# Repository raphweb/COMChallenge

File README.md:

# COMChallenge
Hardware and software parts for the COM challenge.

## Hardware
There is a base board to put up to 8 ESP32-C3 Minis on, including different COM transceivers. Currently, a TJA1050 CAN transceiver is supported. As an extra feature, there is a I²C bus controlled port expander to switch on/off the power for each of the 8 ESP32 modules. A hardware switch can override the port expaneder setting and provide power regardless. The base board can actually run two different COM busses, 4 for the top and 4 for the bottom ESP32 modules.

### Base Board Front:

### Base Board Back:

More details in the [hardware folder](/hardware/).

## Software
There are examples in the [software folder](/software/).

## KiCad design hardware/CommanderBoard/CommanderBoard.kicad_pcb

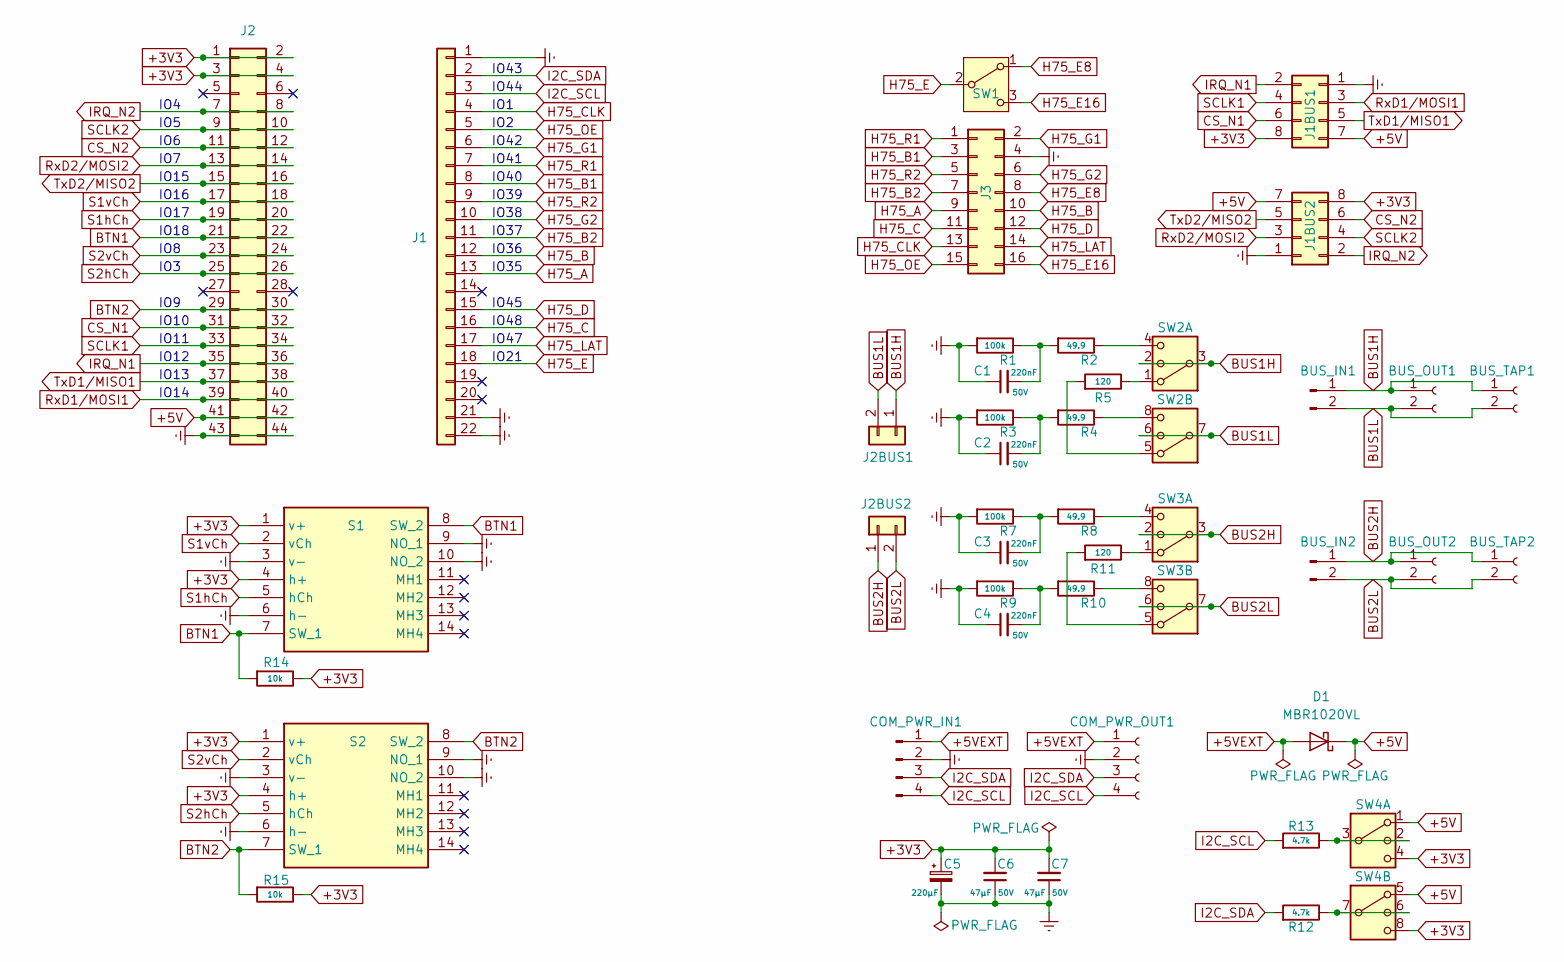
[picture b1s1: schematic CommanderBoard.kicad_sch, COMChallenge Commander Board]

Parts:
BUS_IN1, BUS_IN2: Conn_01x02_Pin; PinHeader_1x02_P2.54mm_Horizontal
BUS_OUT1, BUS_OUT2: Conn_01x02_Socket; PinSocket_1x02_P2.54mm_Horizontal
BUS_TAP1, BUS_TAP2: Conn_01x02_Socket; PinHeader_1x02_P2.54mm_Vertical
C1, C2, C3, C4: 220nF; C_0805_2012Metric; Voltage Rated 50V; Tolerance ±10%; Part CL05B104KB54PNC; LCSC C307331
C5: 220µF; CP_Radial_D6.3mm_P2.50mm
C6, C7: 47µF; C_0805_2012Metric; Voltage Rated 50V; Tolerance ±10%; Part CL05B104KB54PNC; LCSC C307331
COM_PWR_IN1: Conn_01x04_Pin; PinHeader_1x04_P2.54mm_Horizontal
COM_PWR_OUT1: Conn_01x04_Socket; PinSocket_1x04_P2.54mm_Horizontal
D1: MBR1020VL; D_SOD-123F
J1: Conn_01x22; PinSocket_1x22_P2.54mm_Vertical
J1BUS1, J1BUS2: Conn_02x04_Odd_Even; PinSocket_2x04_P2.54mm_Vertical
J2: Conn_02x22; PinSocket_2x22_P2.54mm_Vertical
J2BUS1, J2BUS2: Conn_01x02; PinSocket_1x02_P2.54mm_Vertical
J3: HUB75; IDC-Header_2x08_P2.54mm_Vertical
R1, R3, R7, R9: 100k; R_1206_3216Metric; Overload Voltage Max 200V; Tolerance ±1%; Part 1206W4F1002T5E; LCSC C17902
R2, R4, R8, R10: 49.9; R_1206_3216Metric; Overload Voltage Max 200V; Tolerance ±1%; Part 1206W4F1002T5E; LCSC C17902
R5, R11: 120; R_1206_3216Metric; Overload Voltage Max 200V; Tolerance ±1%; Part 1206W4F1002T5E; LCSC C17902
R12, R13: 4.7k; R_1206_3216Metric; Overload Voltage Max 200V; Tolerance ±1%; Part 1206W4F1002T5E; LCSC C17902
R14, R15: 10k; R_1206_3216Metric; Overload Voltage Max 200V; Tolerance ±1%; Part 1206W4F1002T5E; LCSC C17902
S1, S2: THB001P; Mouser Part Number 611-THB001P
SW1: SW_SPDT; CLSB12B01T
SW2, SW3, SW4: SW_DP3T; CLSB23B01T

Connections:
+3V3: C5.1, C6.2, C7.2, J1BUS1.8, J1BUS2.8, J2.1, J2.2, J2.3, J2.4, R14.1, R15.1, S1.1 (v+), S1.4 (h+), S2.1 (v+), S2.4 (h+), SW4.4, SW4.8
+5V: D1.1 (K), J1BUS1.7, J1BUS2.7, J2.41, J2.42, SW4.1, SW4.5
+5VEXT: COM_PWR_IN1.1, COM_PWR_OUT1.1, D1.2 (A)
BTN1: J2.21, J2.22, R14.2, S1.7 (SW_1), S1.8 (SW_2)
BTN2: J2.29, J2.30, R15.2, S2.7 (SW_1), S2.8 (SW_2)
BUS1H: BUS_IN1.1, BUS_OUT1.1, BUS_TAP1.1, J2BUS1.1, SW2.2, SW2.3
BUS1L: BUS_IN1.2, BUS_OUT1.2, BUS_TAP1.2, J2BUS1.2, SW2.6, SW2.7
BUS2H: BUS_IN2.1, BUS_OUT2.1, BUS_TAP2.1, J2BUS2.1, SW3.2, SW3.3
BUS2L: BUS_IN2.2, BUS_OUT2.2, BUS_TAP2.2, J2BUS2.2, SW3.6, SW3.7
CS_N1: J1BUS1.6, J2.31, J2.32
CS_N2: J1BUS2.6, J2.11, J2.12
GNDREF: C1.1, C2.1, C3.1, C4.1, C5.2, C6.1, C7.1, COM_PWR_IN1.2, COM_PWR_OUT1.2, J1.1, J1.21, J1.22, J1BUS1.1, J1BUS2.1, J2.43, J2.44, J3.4, R1.2, R3.2, R7.2, R9.2, S1.3 (v-), S1.6 (h-), S1.9 (NO_1), S1.10 (NO_2), S2.3 (v-), S2.6 (h-), S2.9 (NO_1), S2.10 (NO_2)
H75_A: J1.13, J3.9
H75_B: J1.12, J3.10
H75_B1: J1.8, J3.3
H75_B2: J1.11, J3.7
H75_C: J1.16, J3.11
H75_CLK: J1.4, J3.13
H75_D: J1.15, J3.12
H75_E: J1.18, SW1.2 (B)
H75_E8: J3.8, SW1.1 (A)
H75_E16: J3.16, SW1.3 (C)
H75_G1: J1.6, J3.2
H75_G2: J1.10, J3.6
H75_LAT: J1.17, J3.14
H75_OE: J1.5, J3.15
H75_R1: J1.7, J3.1
H75_R2: J1.9, J3.5
I2C_SCL: COM_PWR_IN1.4, COM_PWR_OUT1.4, J1.3, R13.2
I2C_SDA: COM_PWR_IN1.3, COM_PWR_OUT1.3, J1.2, R12.2
IRQ_N1: J1BUS1.2, J2.35, J2.36
IRQ_N2: J1BUS2.2, J2.7, J2.8
unnamed: C1.2, R1.1, R2.2
unnamed: C2.2, R3.1, R4.2
unnamed: C3.2, R7.1, R8.2
unnamed: C4.2, R9.1, R10.2
unnamed: R2.1, SW2.4
unnamed: R4.1, SW2.8
unnamed: R5.1, SW2.1
unnamed: R5.2, SW2.5
unnamed: R8.1, SW3.4
unnamed: R10.1, SW3.8
unnamed: R11.1, SW3.1
unnamed: R11.2, SW3.5
unnamed: R12.1, SW4.6, SW4.7
unnamed: R13.1, SW4.2, SW4.3
RxD1/MOSI1: J1BUS1.3, J2.39, J2.40
RxD2/MOSI2: J1BUS2.3, J2.13, J2.14
S1hCh: J2.19, J2.20, S1.5 (hCh)
S1vCh: J2.17, J2.18, S1.2 (vCh)
S2hCh: J2.25, J2.26, S2.5 (hCh)
S2vCh: J2.23, J2.24, S2.2 (vCh)
SCLK1: J1BUS1.4, J2.33, J2.34
SCLK2: J1BUS2.4, J2.9, J2.10
TxD1/MISO1: J1BUS1.5, J2.37, J2.38
TxD2/MISO2: J1BUS2.5, J2.15, J2.16

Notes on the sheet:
IO5
IO47
IO15
IO21
IO7
IO39
IO12
IO2
IO17
IO42
IO44
IO4
IO10
IO45
IO3
IO43
IO9
IO37
IO16
IO18
IO38
IO8
IO40
IO1
IO13
IO14
IO48
IO6
IO35
IO11
IO36
IO41

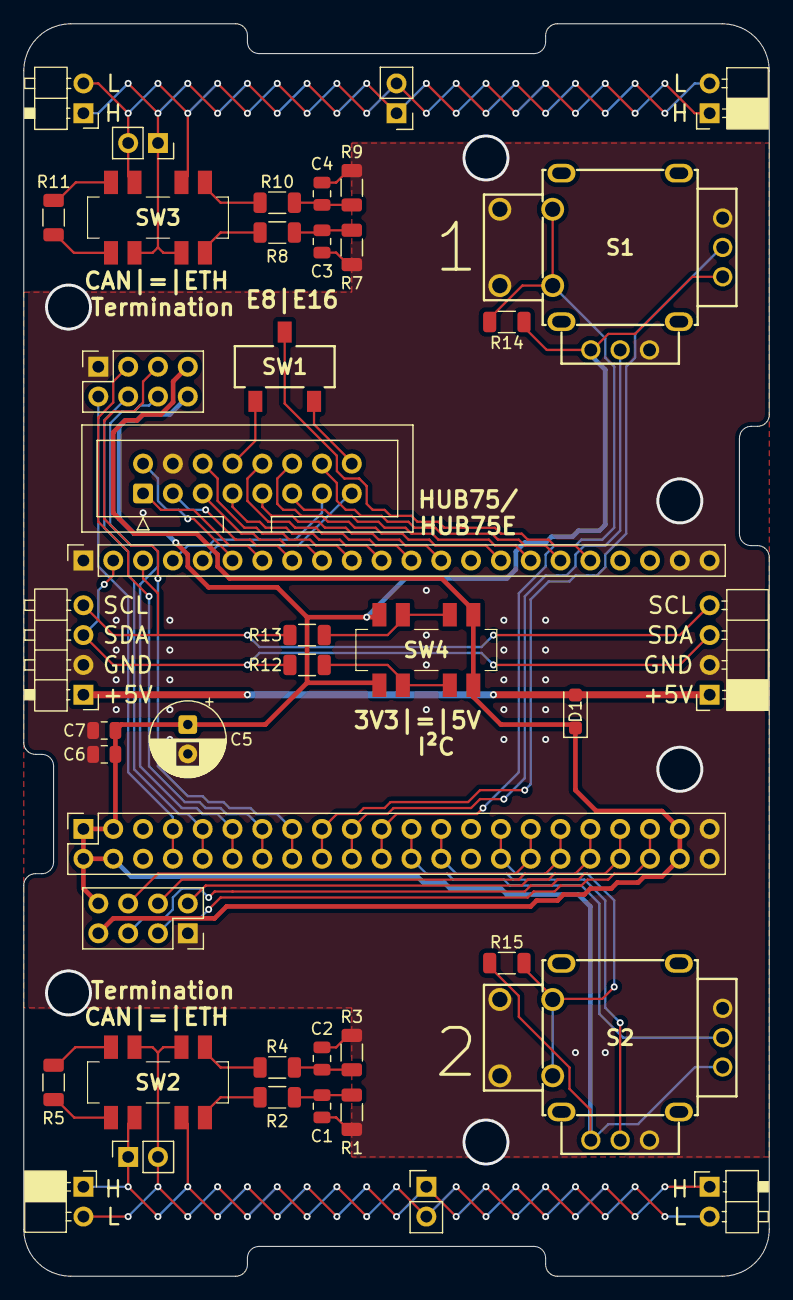
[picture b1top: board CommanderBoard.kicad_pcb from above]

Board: 2 copper layers, 63.5 x 106.7 mm, 43 parts (0 on the bottom side), 56 nets.

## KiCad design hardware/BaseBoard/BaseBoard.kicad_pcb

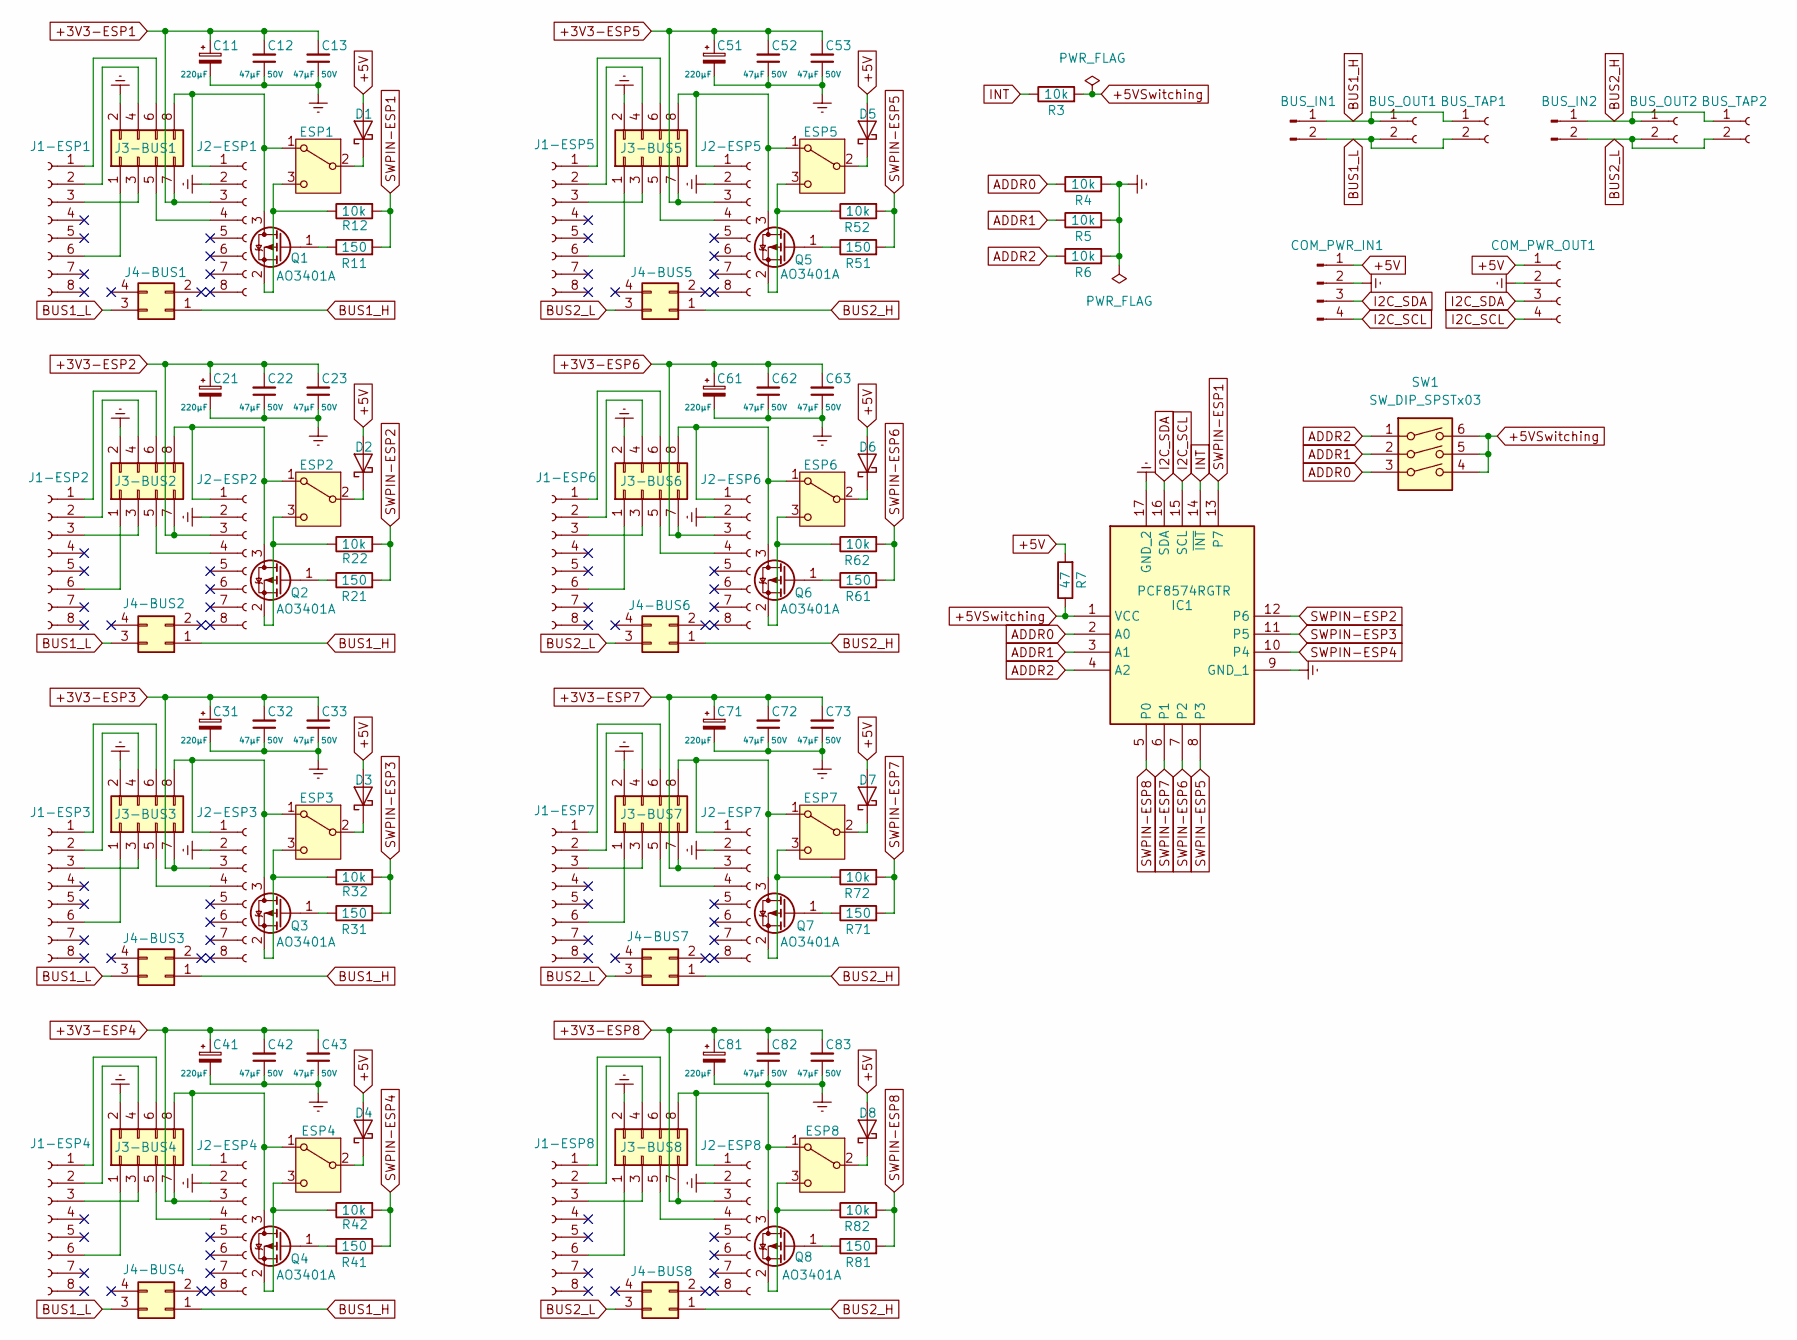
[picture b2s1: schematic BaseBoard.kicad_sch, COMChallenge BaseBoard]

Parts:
BUS_IN1, BUS_IN2: Conn_01x02_Pin; PinHeader_1x02_P2.54mm_Horizontal
BUS_OUT1, BUS_OUT2: Conn_01x02_Socket; PinSocket_1x02_P2.54mm_Horizontal
BUS_TAP1, BUS_TAP2: Conn_01x02_Socket; PinHeader_1x02_P2.54mm_Vertical
C11, C21, C31, C41, C51, C61, C71, C81: 220µF; CP_Radial_D6.3mm_P2.50mm
C12, C13, C22, C23, C32, C33, C42, C43, C52, C53, C62, C63, C72, C73, C82, C83: 47µF; C_0805_2012Metric; Voltage Rated 50V; Tolerance ±10%; Part CL05B104KB54PNC; LCSC C307331
COM_PWR_IN1: Conn_01x04_Pin; PinHeader_1x04_P2.54mm_Horizontal
COM_PWR_OUT1: Conn_01x04_Socket; PinSocket_1x04_P2.54mm_Horizontal
D1, D2, D3, D4, D5, D6, D7, D8: MBR1020VL; D_SOD-123F
ESP1, ESP2, ESP3, ESP4, ESP5, ESP6, ESP7, ESP8: SW_DPDT_XLX_MHPS2285; CLSB12B01T
IC1: PCF8574RGTR; QFN50P300X300X100-17N-D; Mouser Part Number 595-PCF8574RGTR
J1-ESP1, J1-ESP2, J1-ESP3, J1-ESP4, J1-ESP5, J1-ESP6, J1-ESP7, J1-ESP8: ESP-1-L; PinSocket_1x08_P2.54mm_Vertical
J2-ESP1, J2-ESP2, J2-ESP3, J2-ESP4, J2-ESP5, J2-ESP6, J2-ESP7, J2-ESP8: ESP-1-R; PinSocket_1x08_P2.54mm_Vertical
J3-BUS1, J3-BUS2, J3-BUS3, J3-BUS4, J3-BUS5, J3-BUS6, J3-BUS7, J3-BUS8: BUS-IN; Wuerth_WR-PHD_61300825721_Standard_2x04_P2.54mm_Vertical
J4-BUS1, J4-BUS2, J4-BUS3, J4-BUS4, J4-BUS5, J4-BUS6, J4-BUS7, J4-BUS8: BUS-OUT; Wuerth_WR-PHD_61300425721_Standard_2x02_P2.54mm_Vertical
Q1, Q2, Q3, Q4, Q5, Q6, Q7, Q8: AO3401A; SOT-23
R3, R4, R5, R6: 10k; R_0402_1005Metric
R7: 47; R_0603_1608Metric
R11, R21, R31, R41, R51, R61, R71, R81: 150; R_0805_2012Metric
R12, R22, R32, R42, R52, R62, R72, R82: 10k; R_0805_2012Metric
SW1: SW_DIP_SPSTx03; SW_DIP_SPSTx03_Slide_6.7x9.18mm_W8.61mm_P2.54mm_LowProfile

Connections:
+3V3-ESP1: C11.1, C12.2, C13.2, J2-ESP1.3, J3-BUS1.7
+3V3-ESP2: C21.1, C22.2, C23.2, J2-ESP2.3, J3-BUS2.7
+3V3-ESP3: C31.1, C32.2, C33.2, J2-ESP3.3, J3-BUS3.7
+3V3-ESP4: C41.1, C42.2, C43.2, J2-ESP4.3, J3-BUS4.7
+3V3-ESP5: C51.1, C52.2, C53.2, J2-ESP5.3, J3-BUS5.7
+3V3-ESP6: C61.1, C62.2, C63.2, J2-ESP6.3, J3-BUS6.7
+3V3-ESP7: C71.1, C72.2, C73.2, J2-ESP7.3, J3-BUS7.7
+3V3-ESP8: C81.1, C82.2, C83.2, J2-ESP8.3, J3-BUS8.7
+5V: COM_PWR_IN1.1, COM_PWR_OUT1.1, D1.2 (A), D2.2 (A), D3.2 (A), D4.2 (A), D5.2 (A), D6.2 (A), D7.2 (A), D8.2 (A), R7.2
+5VSwitching: IC1.1 (VCC), R3.2, R7.1, SW1.4, SW1.5, SW1.6
ADDR0: IC1.2 (A0), R4.1, SW1.3
ADDR1: IC1.3 (A1), R5.1, SW1.2
ADDR2: IC1.4 (A2), R6.1, SW1.1
BUS1_H: BUS_IN1.1, BUS_OUT1.1, BUS_TAP1.1, J4-BUS1.1, J4-BUS2.1, J4-BUS3.1, J4-BUS4.1
BUS1_L: BUS_IN1.2, BUS_OUT1.2, BUS_TAP1.2, J4-BUS1.3, J4-BUS2.3, J4-BUS3.3, J4-BUS4.3
BUS2_H: BUS_IN2.1, BUS_OUT2.1, BUS_TAP2.1, J4-BUS5.1, J4-BUS6.1, J4-BUS7.1, J4-BUS8.1
BUS2_L: BUS_IN2.2, BUS_OUT2.2, BUS_TAP2.2, J4-BUS5.3, J4-BUS6.3, J4-BUS7.3, J4-BUS8.3
GNDREF: C11.2, C12.1, C13.1, C21.2, C22.1, C23.1, C31.2, C32.1, C33.1, C41.2, C42.1, C43.1, C51.2, C52.1, C53.1, C61.2, C62.1, C63.1, C71.2, C72.1, C73.1, C81.2, C82.1, C83.1, COM_PWR_IN1.2, COM_PWR_OUT1.2, IC1.9 (GND_1), IC1.17 (GND_2), J2-ESP1.2, J2-ESP2.2, J2-ESP3.2, J2-ESP4.2, J2-ESP5.2, J2-ESP6.2, J2-ESP7.2, J2-ESP8.2, J3-BUS1.2, J3-BUS2.2, J3-BUS3.2, J3-BUS4.2, J3-BUS5.2, J3-BUS6.2, J3-BUS7.2, J3-BUS8.2, R4.2, R5.2, R6.2
I2C_SCL: COM_PWR_IN1.4, COM_PWR_OUT1.4, IC1.15 (SCL)
I2C_SDA: COM_PWR_IN1.3, COM_PWR_OUT1.3, IC1.16 (SDA)
INT: IC1.14 (~INT), R3.1
unnamed: D1.1 (K), ESP1.2 (B)
unnamed: D2.1 (K), ESP2.2 (B)
unnamed: D3.1 (K), ESP3.2 (B)
unnamed: D4.1 (K), ESP4.2 (B)
unnamed: D5.1 (K), ESP5.2 (B)
unnamed: D6.1 (K), ESP6.2 (B)
unnamed: D7.1 (K), ESP7.2 (B)
unnamed: D8.1 (K), ESP8.2 (B)
unnamed: ESP1.1 (A), J2-ESP1.1, J3-BUS1.8, Q1.3 (D)
unnamed: ESP1.3 (C), Q1.2 (S), R12.1
unnamed: ESP2.1 (A), J2-ESP2.1, J3-BUS2.8, Q2.3 (D)
unnamed: ESP2.3 (C), Q2.2 (S), R22.1
unnamed: ESP3.1 (A), J2-ESP3.1, J3-BUS3.8, Q3.3 (D)
unnamed: ESP3.3 (C), Q3.2 (S), R32.1
unnamed: ESP4.1 (A), J2-ESP4.1, J3-BUS4.8, Q4.3 (D)
unnamed: ESP4.3 (C), Q4.2 (S), R42.1
unnamed: ESP5.1 (A), J2-ESP5.1, J3-BUS5.8, Q5.3 (D)
unnamed: ESP5.3 (C), Q5.2 (S), R52.1
unnamed: ESP6.1 (A), J2-ESP6.1, J3-BUS6.8, Q6.3 (D)
unnamed: ESP6.3 (C), Q6.2 (S), R62.1
unnamed: ESP7.1 (A), J2-ESP7.1, J3-BUS7.8, Q7.3 (D)
unnamed: ESP7.3 (C), Q7.2 (S), R72.1
unnamed: ESP8.1 (A), J2-ESP8.1, J3-BUS8.8, Q8.3 (D)
unnamed: ESP8.3 (C), Q8.2 (S), R82.1
unnamed: J1-ESP1.1, J3-BUS1.6
unnamed: J1-ESP1.2, J3-BUS1.4
unnamed: J1-ESP1.3, J3-BUS1.3
unnamed: J1-ESP1.6, J3-BUS1.1
unnamed: J1-ESP2.1, J3-BUS2.6
unnamed: J1-ESP2.2, J3-BUS2.4
unnamed: J1-ESP2.3, J3-BUS2.3
unnamed: J1-ESP2.6, J3-BUS2.1
unnamed: J1-ESP3.1, J3-BUS3.6
unnamed: J1-ESP3.2, J3-BUS3.4
unnamed: J1-ESP3.3, J3-BUS3.3
unnamed: J1-ESP3.6, J3-BUS3.1
unnamed: J1-ESP4.1, J3-BUS4.6
unnamed: J1-ESP4.2, J3-BUS4.4
unnamed: J1-ESP4.3, J3-BUS4.3
unnamed: J1-ESP4.6, J3-BUS4.1
unnamed: J1-ESP5.1, J3-BUS5.6
unnamed: J1-ESP5.2, J3-BUS5.4
unnamed: J1-ESP5.3, J3-BUS5.3
unnamed: J1-ESP5.6, J3-BUS5.1
unnamed: J1-ESP6.1, J3-BUS6.6
unnamed: J1-ESP6.2, J3-BUS6.4
unnamed: J1-ESP6.3, J3-BUS6.3
unnamed: J1-ESP6.6, J3-BUS6.1
unnamed: J1-ESP7.1, J3-BUS7.6
unnamed: J1-ESP7.2, J3-BUS7.4
unnamed: J1-ESP7.3, J3-BUS7.3
unnamed: J1-ESP7.6, J3-BUS7.1
unnamed: J1-ESP8.1, J3-BUS8.6
unnamed: J1-ESP8.2, J3-BUS8.4
unnamed: J1-ESP8.3, J3-BUS8.3
unnamed: J1-ESP8.6, J3-BUS8.1
unnamed: J2-ESP1.4, J3-BUS1.5
unnamed: J2-ESP2.4, J3-BUS2.5
unnamed: J2-ESP3.4, J3-BUS3.5
unnamed: J2-ESP4.4, J3-BUS4.5
unnamed: J2-ESP5.4, J3-BUS5.5
unnamed: J2-ESP6.4, J3-BUS6.5
unnamed: J2-ESP7.4, J3-BUS7.5
unnamed: J2-ESP8.4, J3-BUS8.5
unnamed: Q1.1 (G), R11.1
unnamed: Q2.1 (G), R21.1
unnamed: Q3.1 (G), R31.1
unnamed: Q4.1 (G), R41.1
unnamed: Q5.1 (G), R51.1
unnamed: Q6.1 (G), R61.1
unnamed: Q7.1 (G), R71.1
unnamed: Q8.1 (G), R81.1
SWPIN-ESP1: IC1.13 (P7), R11.2, R12.2
SWPIN-ESP2: IC1.12 (P6), R21.2, R22.2
SWPIN-ESP3: IC1.11 (P5), R31.2, R32.2
SWPIN-ESP4: IC1.10 (P4), R41.2, R42.2
SWPIN-ESP5: IC1.8 (P3), R51.2, R52.2
SWPIN-ESP6: IC1.7 (P2), R61.2, R62.2
SWPIN-ESP7: IC1.6 (P1), R71.2, R72.2
SWPIN-ESP8: IC1.5 (P0), R81.2, R82.2

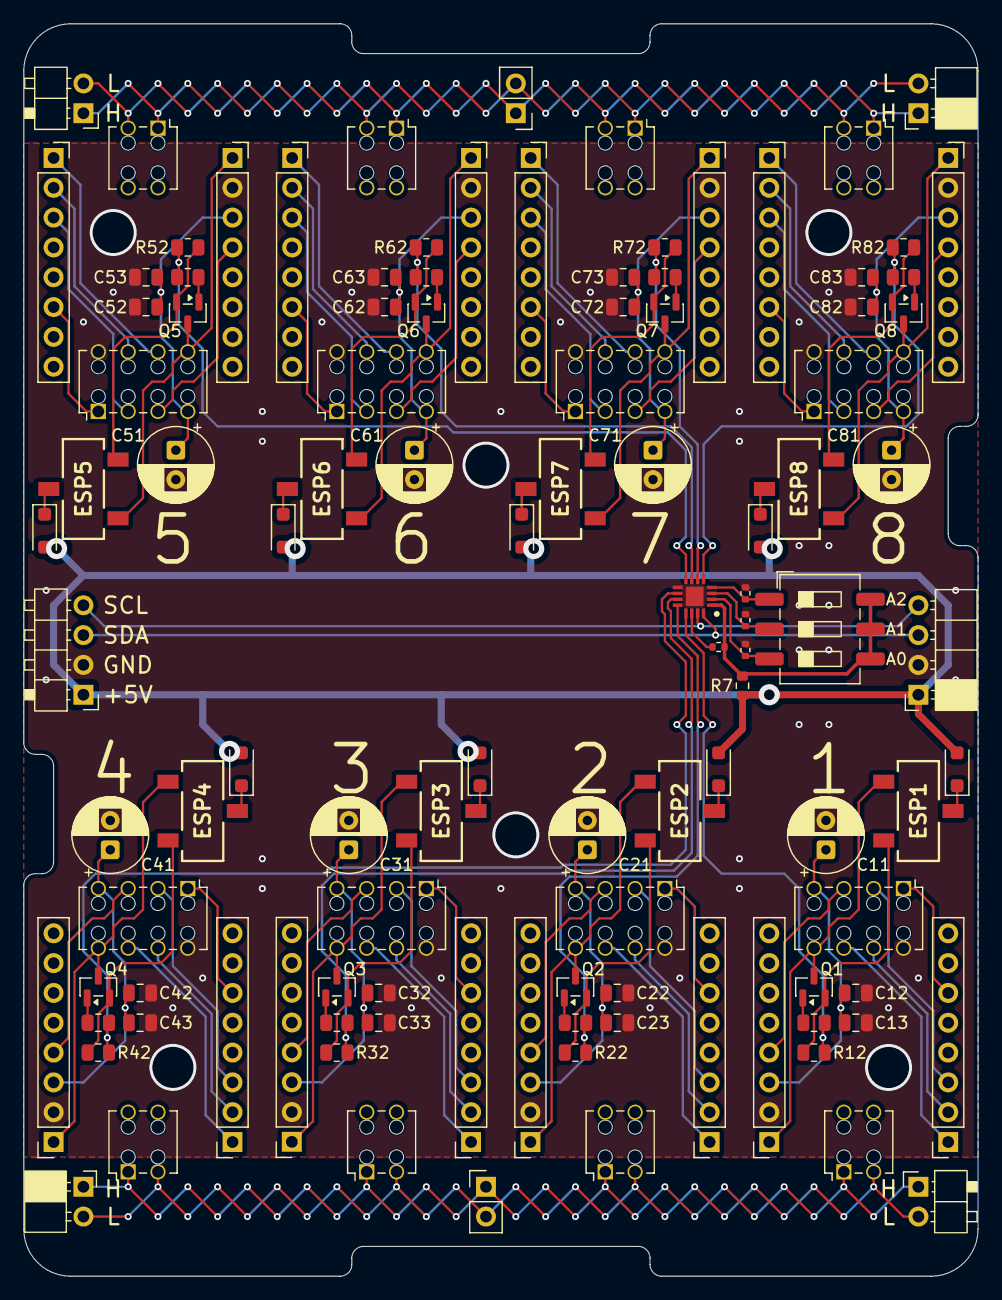
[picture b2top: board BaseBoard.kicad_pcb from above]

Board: 2 copper layers, 81.3 x 106.7 mm, 111 parts (0 on the bottom side), 101 nets.

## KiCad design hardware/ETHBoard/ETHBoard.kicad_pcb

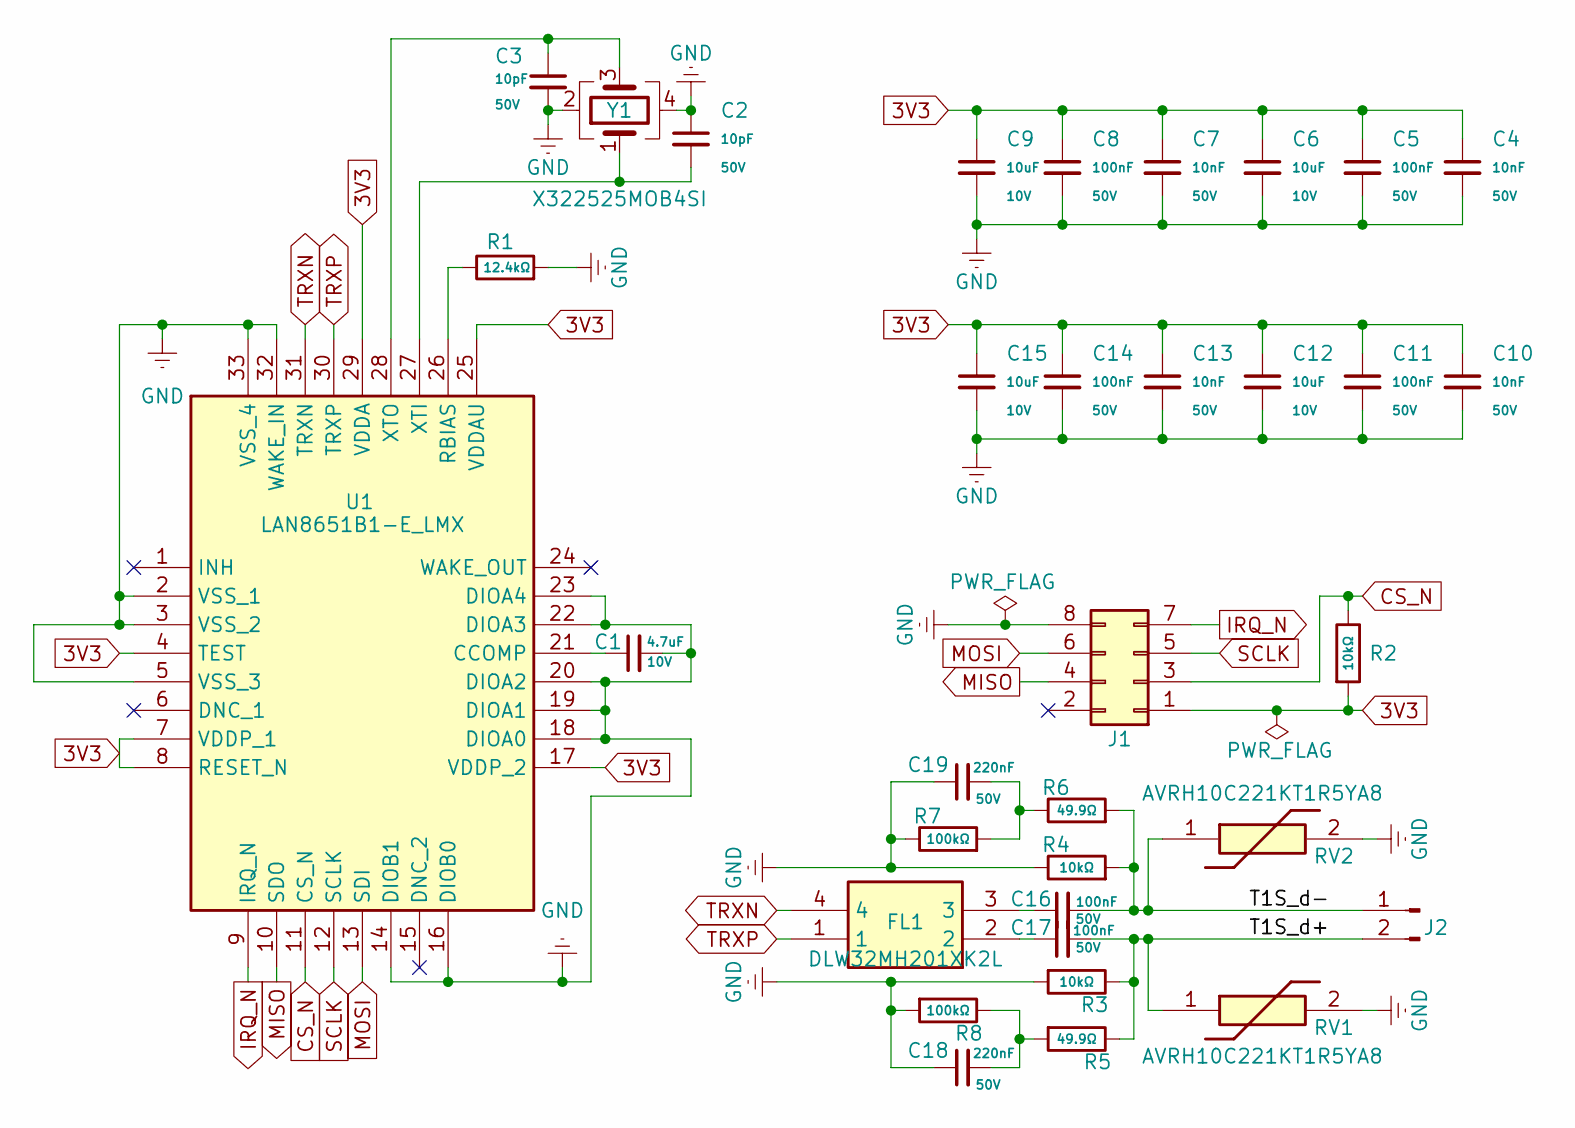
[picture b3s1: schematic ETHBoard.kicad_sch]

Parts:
C1: 4.7uF; C_0603_1608Metric; Voltage Rated 10V; Tolerance ±20%; Part CL05A475MP5NRNC; LCSC C23733
C2, C3: 10pF; C_0402_1005Metric; Voltage Rated 50V; Tolerance ±5%; Part CL05C100JB5NNNC; LCSC C32949
C4, C7, C10, C13: 10nF; C_0402_1005Metric; Voltage Rated 50V; Tolerance ±10%; Part CL05B103KB5NNNC; LCSC C15195
C5, C8, C11, C14: 100nF; C_0402_1005Metric; Voltage Rated 50V; Tolerance ±10%; Part CL05B104KB54PNC; LCSC C307331
C6: 10uF; C_0402_1005Metric; Voltage Rated 10V; Tolerance ±10%; Part CL05B103KB5NNNC; LCSC C15195
C9, C12, C15: 10uF; C_0402_1005Metric; Voltage Rated 10V; Tolerance ±10%; Part CL10A106KP8NNNC; LCSC C19702
C16, C17: 100nF; C_0603_1608Metric; Voltage Rated 50V; Tolerance ±10%; Part CL05B104KB54PNC; LCSC C307331
C18, C19: 220nF; C_0805_2012Metric; Voltage Rated 50V; Tolerance ±10%; Part CL05B104KB54PNC; LCSC C307331
FL1: DLW32MH201XK2L; DLW32MH101XK2L; Mouser Part Number 81-DLW32MH201XK2L
J1: Conn_02x04_Odd_Even; PinHeader_2x04_P2.54mm_Vertical
J2: Conn_01x02_Pin; PinHeader_1x02_P2.54mm_Vertical
R1: 12.4kΩ; R_0402_1005Metric; Tolerance 1%
R2: 10kΩ; R_0402_1005Metric; Overload Voltage Max 75V; Tolerance ±1%; Part 0603WAF1002T5E; LCSC C25804
R3, R4: 10kΩ; R_1206_3216Metric; Overload Voltage Max 200V; Tolerance ±1%; Part 1206W4F1002T5E; LCSC C17902
R5, R6: 49.9Ω; R_1206_3216Metric; Overload Voltage Max 200V; Tolerance ±1%; Part 1206W4F1002T5E; LCSC C17902
R7, R8: 100kΩ; R_1206_3216Metric; Overload Voltage Max 200V; Tolerance ±1%; Part 1206W4F1002T5E; LCSC C17902
RV1, RV2: AVRH10C221KT1R5YA8; RESC1005X55N; Mouser Part Number 810-AVRH10C221K1R5YA
U1: LAN8651B1-E_LMX; QFN50P500X500X100-33N-D; Manufacturer_Part_Number LAN8651B1-E/LMX; Mouser Part Number 579-LAN8651B1-E/LMX
Y1: X322525MOB4SI; Crystal_SMD_3225-4Pin_3.2x2.5mm; Frequency Tolerance ±10ppm; Part X322525MOB4SI; LCSC C9006

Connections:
3V3: C4.1, C5.1, C6.1, C7.1, C8.1, C9.1, C10.1, C11.1, C12.1, C13.1, C14.1, C15.1, J1.1, R2.2, U1.4 (TEST), U1.7 (VDDP_1), U1.8 (RESET_N), U1.17 (VDDP_2), U1.25 (VDDAU), U1.29 (VDDA)
/T1S_d+: C17.2, J2.2, R3.1, R5.1, RV1.1
/T1S_d-: C16.2, J2.1, R4.2, R6.2, RV2.1
CS_N: J1.3, R2.1, U1.11 (CS_N)
GND: C1.2, C2.1, C3.2, C4.2, C5.2, C6.2, C7.2, C8.2, C9.2, C10.2, C11.2, C12.2, C13.2, C14.2, C15.2, C18.1, C19.1, J1.8, R1.2, R3.2, R4.1, R7.1, R8.2, RV1.2, RV2.2, U1.2 (VSS_1), U1.3 (VSS_2), U1.5 (VSS_3), U1.14 (DIOB1), U1.16 (DIOB0), U1.18 (DIOA0), U1.19 (DIOA1), U1.20 (DIOA2), U1.22 (DIOA3), U1.23 (DIOA4), U1.32 (WAKE_IN), U1.33 (VSS_4), Y1.2, Y1.4
IRQ_N: J1.7, U1.9 (IRQ_N)
MISO: J1.4, U1.10 (SDO)
MOSI: J1.6, U1.13 (SDI)
unnamed: C16.1, FL1.3
unnamed: C17.1, FL1.2
unnamed: C18.2, R5.2, R8.1
unnamed: C19.2, R6.1, R7.2
unnamed: C1.1, U1.21 (CCOMP)
unnamed: R1.1, U1.26 (RBIAS)
unnamed: C2.2, U1.27 (XTI), Y1.1
unnamed: C3.1, U1.28 (XTO), Y1.3
SCLK: J1.5, U1.12 (SCLK)
TRXN: FL1.4, U1.31 (TRXN)
TRXP: FL1.1, U1.30 (TRXP)

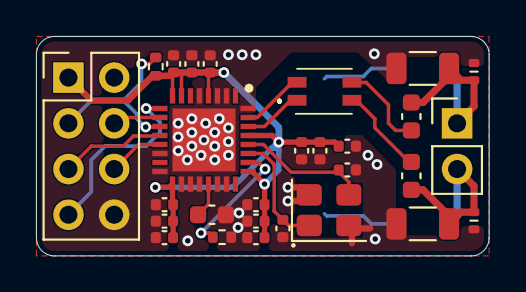
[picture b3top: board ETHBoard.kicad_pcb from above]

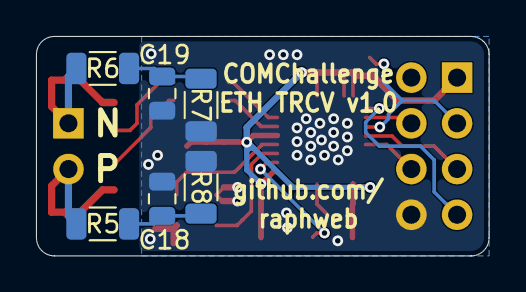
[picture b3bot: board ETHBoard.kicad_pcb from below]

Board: 2 copper layers, 25.1 x 12.2 mm, 34 parts (6 on the bottom side), 19 nets.

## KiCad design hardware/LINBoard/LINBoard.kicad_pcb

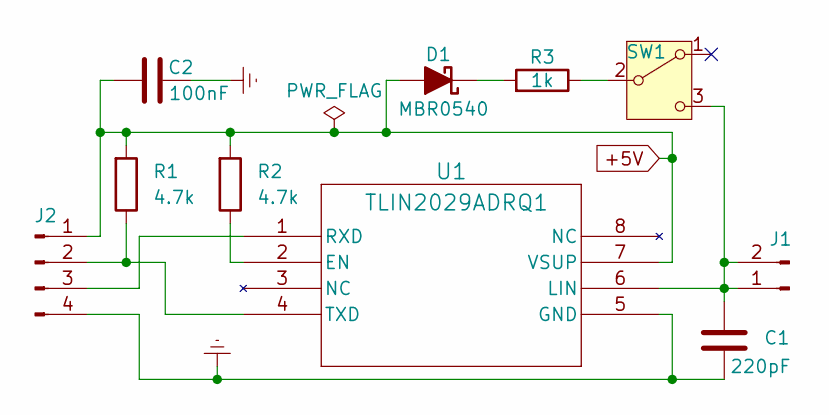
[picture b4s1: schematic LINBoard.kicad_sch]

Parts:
C1: 220pF; C_0805_2012Metric
C2: 100nF; C_0805_2012Metric
D1: MBR0540; D_SOD-123
J1: Conn_01x02_Pin; PinHeader_1x02_P2.54mm_Vertical
J2: PinHeader_1x04_P2.54mm_Vertical
R1, R2: 4.7k; R_0805_2012Metric
R3: 1k; R_0805_2012Metric
SW1: SW_SPDT; SW_SPDT_Shouhan_MSK12C02
U1: TLIN2029ADRQ1; SOIC8_D_TEX

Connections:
+5V: C2.1, D1.2 (A), J2.1, R1.1, R2.1, U1.7 (VSUP)
GNDREF: C1.2, C2.2, J2.4, U1.5 (GND)
unnamed: D1.1 (K), R3.1
unnamed: C1.1, J1.1, J1.2, SW1.3 (C), U1.6 (LIN)
unnamed: J2.2, R1.2, U1.4 (TXD)
unnamed: J2.3, U1.1 (RXD)
unnamed: R3.2, SW1.2 (B)
unnamed: R2.2, U1.2 (EN)

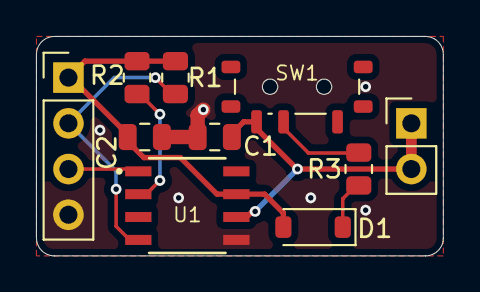
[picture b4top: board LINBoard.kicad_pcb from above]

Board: 2 copper layers, 22.6 x 12.2 mm, 10 parts (0 on the bottom side), 8 nets.

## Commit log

2025-10-12 First ESP32C3 test.
2025-10-26 Added initial KiCad base board version.
2025-10-26 Fixed wrong width of ESP modules.
2025-11-04 Small optimizations.
2025-11-08 Added some more labels.
2025-11-11 Replaced two one row headers with one two row header.
2025-11-12 Added KiBot GH action.
2025-11-12 Cosmetics.
2025-11-16 Add initial version of LINBoard.
2025-11-30 Shrunk LINBoard.
2025-11-30 Removed gerbers.
2025-12-05 Added small CAN message example.
2026-01-15 ETHBoard first tryout.
2026-01-15 Minor ETHBoard tweaks.
2026-01-15 Added ETHBoard KiCAD action.
2026-01-16 Update ETHBoard.
2026-01-16 Reverted back to using std lib (not jlcpcb).
2026-01-16 More cleanup, pipline should run now.
2026-01-17 Renamed stp files to step.
2026-01-17 BaseBoard v1.1 update.
2026-01-17 Enlarged smallest SMD resistors.
2026-01-17 Readded preview pictures of the base board.
2026-01-17 Fixed vias in small pads.
2026-01-21 Rework ETHBoard.
2026-01-21 Added common mode choke.
2026-01-22 Corrected footprints of varistors.
2026-01-23 Simplified BaseBoard.
2026-02-01 Minor BaseBoard updates.
2026-02-01 Added termination parts for ETHBoard.
2026-02-07 Larger resistors and more GND vias.
2026-02-07 Updated BaseBoard pictures.
2026-02-07 Trigger actions.
2026-02-07 Trigger actions again.
2026-02-22 Added first try of CommanderBoard.
2026-02-22 Reworked Commanderboard, horizontal orientation of the ESP32-S3.
2026-02-22 Updated step files for all boards, footprints for LINBoard.
2026-02-25 Added two joysticks to CommanderBoard.
2026-03-26 Added software for thumbstick test.
2026-03-26 Added second thumbstick, buttons, and pretty printing.
2026-03-26 Even prettier now :-)
2026-03-31 Removed pull-up resistors for I2C slaves.
2026-04-03 Small ThumbstickTest updates.
2026-04-03 First working version of HackaTRON.
2026-04-05 Gave thumbstuck #1 a bit more space.
2026-04-06 Fixed nasty memory leak in replay.
2026-04-06 Minor improvements.
2026-04-06 Fixed another memory leak, added animations and game files.
2026-04-06 Implemented probing connected nodes.
2026-04-13 Added diodes to base board.
2026-04-14 Added capacitors for +3V3 stabilization.
2026-04-14 Added I2C passthrough (listener) mode.
2026-04-14 Improved isolation of bus connections.
2026-04-19 Updated BaseBoard to kicad v10.
2026-04-19 Updated Commanderboard to kicad v10. Added pcis.
2026-04-19 Updated ETHboard to kicad v10. Added pcis.
2026-04-19 Updated LINboard to kicad v10. Added pcis.
2026-04-26 Minor imrpovements in positions and footprints.
2026-04-26 Removed unused switch lib.
2026-04-26 Added .history (created by KiCad10) folders to gitignore.
2026-04-26 ETHBoard: Slightly moved bottom side components.
2026-04-26 Updated ETHBoard pictures.
2026-05-10 Removed ThumbstickTest. Minor pcb cosmetics.
2026-05-10 Added 3D printed parts (compatible with v1.0 of the pcbs).
2026-05-10 PCB cosmetics.
2026-05-10 Added more UI for node probing.
